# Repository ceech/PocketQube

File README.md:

# PocketQube
CadSoft Eagle files for PocketQube satellite

Done in collaboration with ArduOrbiter

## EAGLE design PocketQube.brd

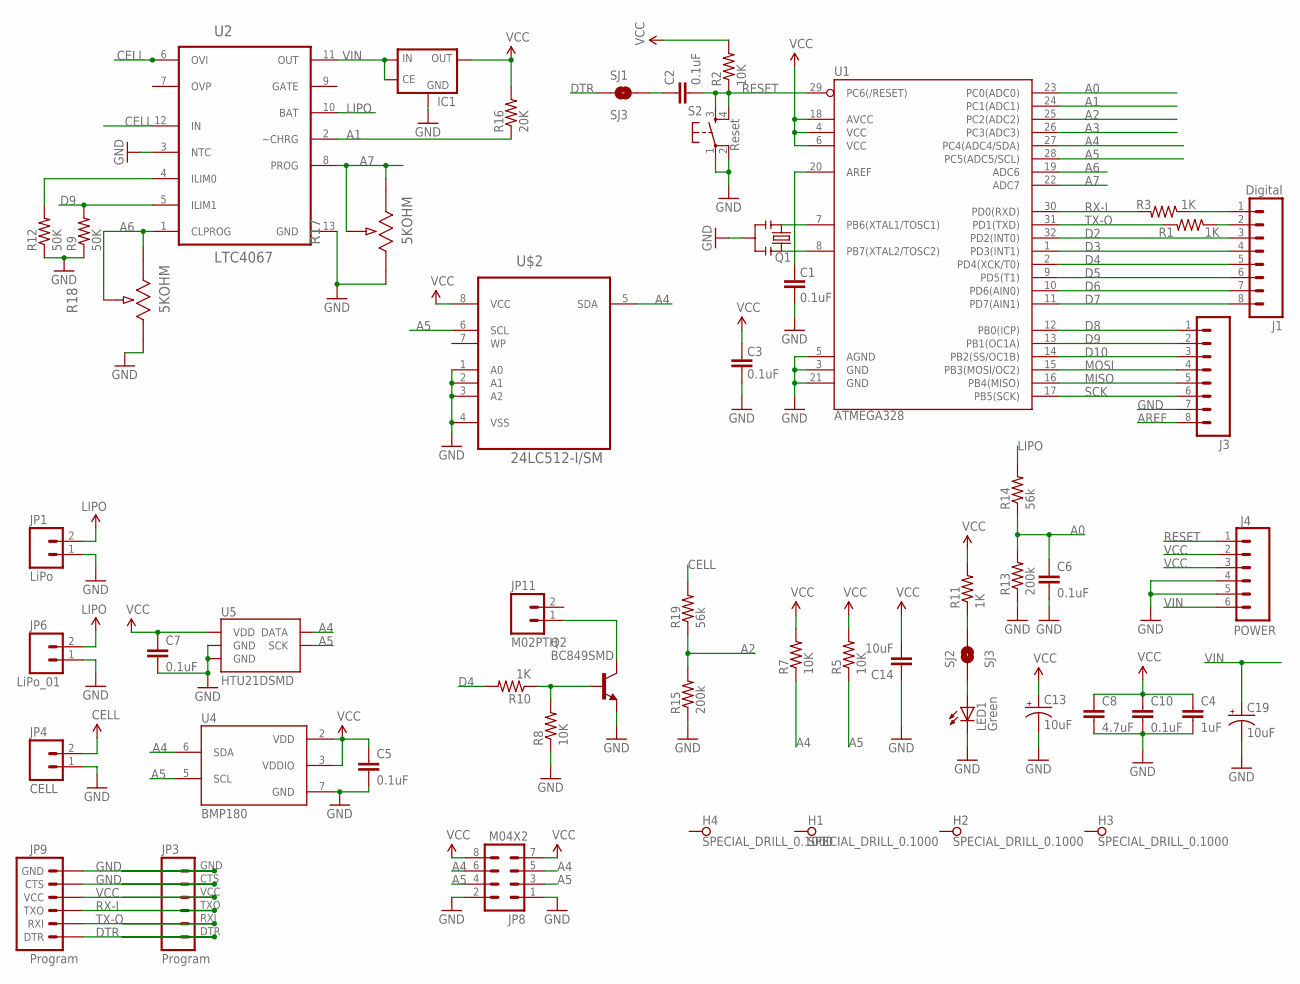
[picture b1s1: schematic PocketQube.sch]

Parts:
C1, C2, C3, C5, C6, C7, C10: 0.1uF; 0805
C4: 1uF; 0805
C8: 4.7uF; 0805
C13, C19: 10uF; EIA3216
C14: 10uF; 0805
H1, H2, H3, H4: SPECIAL_DRILL_0.1000; PAD_0.1000
IC1: XC63FPP; SOT89R
J1: Digital; 1X08
J3: M081X08; 1X08
J4: POWER; 1X06
JP1: LiPo; 1X02
JP3: Program; 1X06
JP4: CELL; 1X02
JP6: LiPo_01; 1X02
JP8: M04X2; 2X4
JP9: Program; 1X06-SMD
JP11: M02PTH; 1X02
LED1: Green; PLCC2
Q1: 8MHZ; RESONATOR-SMD
Q2: BC849SMD; SOT23-BEC
R1, R3, R10, R11: 1K; 0805
R2, R5, R7, R8: 10K; 0805
R9, R12: 50K; 0805
R13, R15: 200k; 0805
R14, R19: 56k; 0805
R16: 20K; 0805
R17, R18: 5KOHM; POT_EVM2N
S2: Reset; TACTILE_SWITCH_SMD
SJ1, SJ2: SJ3; SJ_2S-NOTRACE
U1: ATMEGA328; TQFP32-08
U2: LTC4067; DFN300X300X80-13N
U4: BMP180
U5: HTU21DSMD; HTU21D
U$2: 24LC512-I/SM; SOIC127P794X203-8N

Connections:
A0: C6.1, R13.2, R14.1, U1.23 (PC0(ADC0))
A1: R16.1, U1.24 (PC1(ADC1)), U2.2 (~CHRG)
A2: R15.2, R19.1, U1.25 (PC2(ADC2))
A3: U1.26 (PC3(ADC3))
A4: JP8.5, JP8.6, R7.1, U1.27 (PC4(ADC4/SDA)), U4.6 (SDA), U5.DATA, U$2.5 (SDA)
A5: JP8.3, JP8.4, R5.1, U1.28 (PC5(ADC5/SCL)), U4.5 (SCL), U5.SCK, U$2.6 (SCL)
A6: R18.2, R18.3, U1.19 (ADC6), U2.1 (CLPROG)
A7: R17.2, R17.3, U1.22 (ADC7), U2.8 (PROG)
AREF: C1.2, J3.8, U1.20 (AREF)
CELL: JP4.2, R19.2, U2.6 (OVI), U2.12 (IN)
D2: J1.3, U1.32 (PD2(INT0))
D3: J1.4, U1.1 (PD3(INT1))
D4: J1.5, R10.2, U1.2 (PD4(XCK/T0))
D5: J1.6, U1.9 (PD5(T1))
D6: J1.7, U1.10 (PD6(AIN0))
D7: J1.8, U1.11 (PD7(AIN1))
D8: J3.1, U1.12 (PB0(ICP))
D9: J3.2, R9.2, U1.13 (PB1(OC1A)), U2.5 (ILIM1)
D10: J3.3, U1.14 (PB2(SS/OC1B))
DTR: JP3.DTR (1), JP9.1 (DTR), SJ1.1
GND: C1.1, C3.1, C4.2, C5.2, C6.2, C7.2, C8.2, C10.2, C13.C (-), C14.1, C19.C (-), IC1.2 (GND), J3.7, J4.4, J4.5, JP1.1, JP3.CTS (5), JP3.GND (6), JP4.1, JP6.1, JP8.1, JP8.2, JP9.5 (CTS), JP9.6 (GND), LED1.C, Q1.2, Q2.E, R8.1, R9.1, R12.1, R13.1, R15.1, R17.1, R18.1, S2.1, S2.2, U1.3 (GND), U1.5 (AGND), U1.21 (GND), U2.3 (NTC), U2.13 (GND), U4.7 (GND), U5.7 (GND), U5.GND, U$2.1 (A0), U$2.2 (A1), U$2.3 (A2), U$2.4 (VSS)
LIPO: JP1.2, JP6.2, R14.2, U2.10 (BAT)
MISO: J3.5, U1.16 (PB4(MISO))
MOSI: J3.4, U1.15 (PB3(MOSI/OC2))
unnamed: C2.1, SJ1.2
unnamed: Q1.1, U1.8 (PB7(XTAL2/TOSC2))
unnamed: Q1.3, U1.7 (PB6(XTAL1/TOSC1))
unnamed: LED1.A, SJ2.1
unnamed: R11.1, SJ2.2
unnamed: JP11.1, Q2.C
unnamed: Q2.B, R8.2, R10.1
unnamed: R12.2, U2.4 (ILIM0)
RESET: C2.2, J4.1, R2.1, S2.3, S2.4, U1.29 (PC6(/RESET))
RX-I: JP3.TXO (3), JP9.3 (TXO), R3.2, U1.30 (PD0(RXD))
RX-IP: J1.2, R1.1
SCK: J3.6, U1.17 (PB5(SCK))
TX-O: JP3.RXI (2), JP9.2 (RXI), R1.2, U1.31 (PD1(TXD))
TX-OP: J1.1, R3.1
VCC: C3.2, C4.1, C5.1, C7.1, C8.1, C10.1, C13.A (+), C14.2, IC1.5 (OUT), J4.2, J4.3, JP3.VCC (4), JP8.7, JP8.8, JP9.4 (VCC), R2.2, R5.2, R7.2, R11.2, R16.2, U1.4 (VCC), U1.6 (VCC), U1.18 (AVCC), U4.2 (VDD), U4.3 (VDDIO), U5.VDD, U$2.8 (VCC)
VIN: C19.A (+), IC1.1 (CE), IC1.4 (IN), J4.6, U2.11 (OUT)

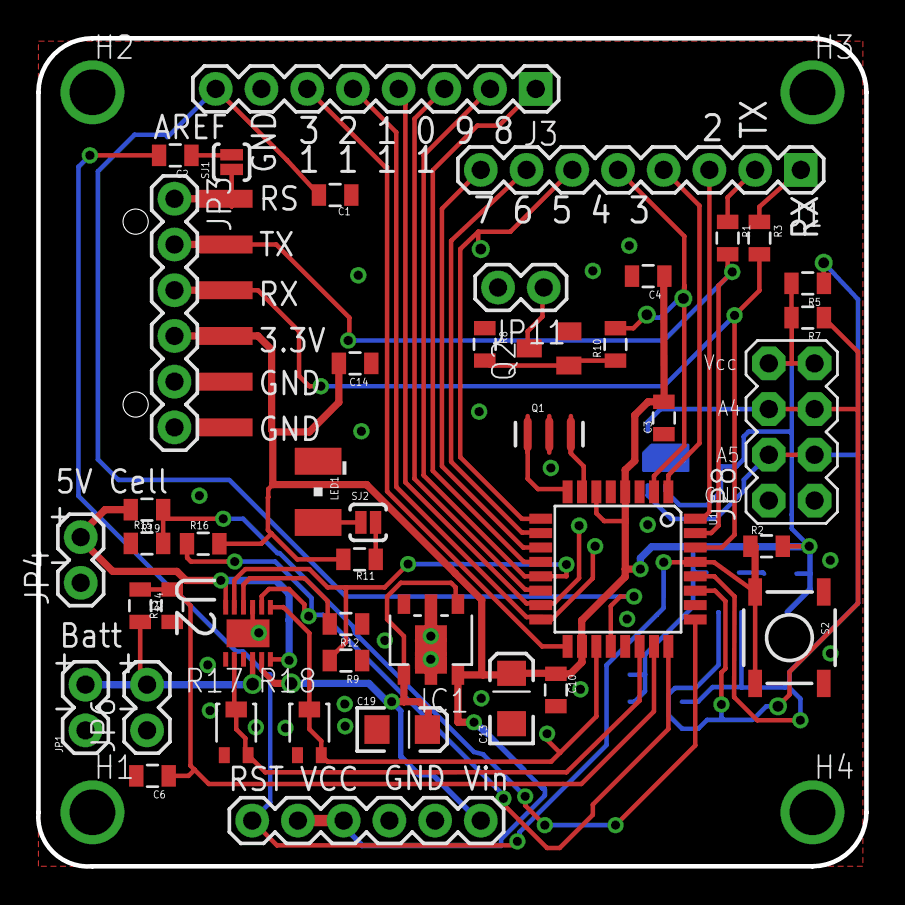
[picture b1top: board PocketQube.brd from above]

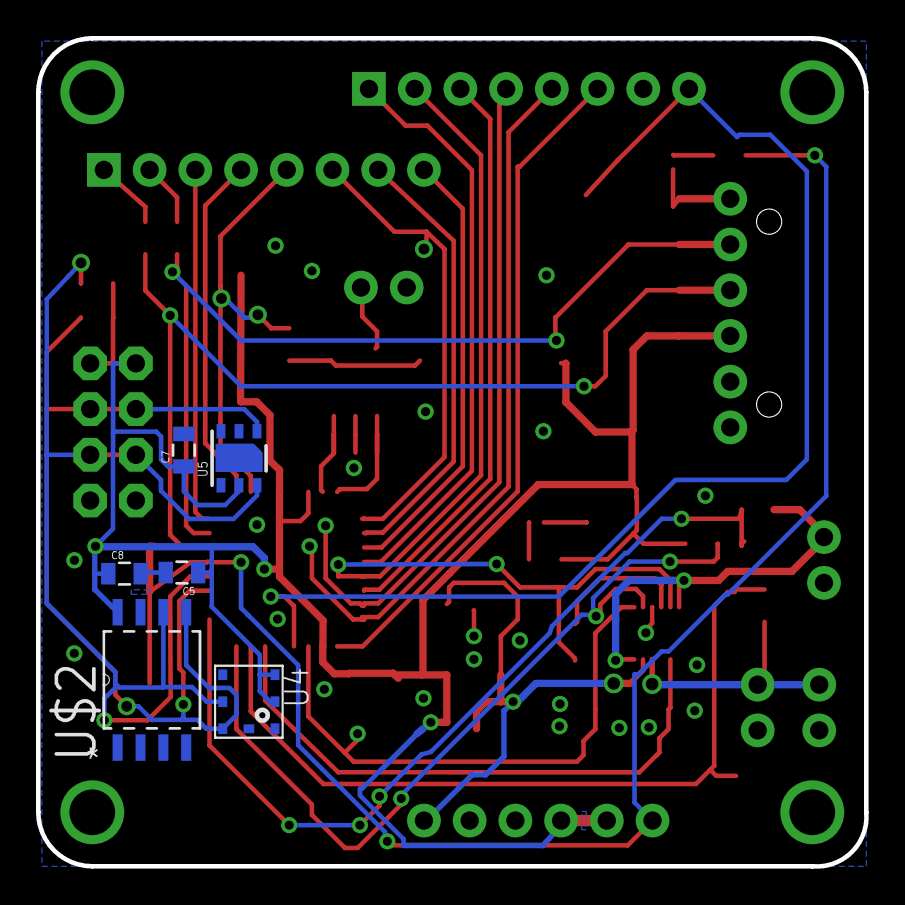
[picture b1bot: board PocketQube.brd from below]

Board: 2 copper layers, 46.0 x 46.0 mm, 55 parts (6 on the bottom side), 39 nets.

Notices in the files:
parts and their libraries:
SparkFun-Connectors: Licensing: Creative Commons ShareAlike 4.0 International - https://creativecommons.org/licenses/by-sa/4.0
